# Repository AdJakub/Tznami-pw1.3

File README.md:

# Tznami-pw1.3
60% keyboard made for the half life project, week1 PCB.

## Why this?
I need a keyboard that will sit nicely on my desk setup, this one thanks to its custom usb slot placement will accomodate my cable management perfectly. 

## PCB
Schematic and PCB Made in kicad.
Schematic            |  PCB
:-------------------------:|:-------------------------:
  |  !

## Case
Made using fusion, using a sandwich mount and an oled mounting mechanism!

Uses stemma QT to connect the oled. connector to MCU and stripped cables soldered to the oled.

## Firmware

Comes with QMK and Vial support.

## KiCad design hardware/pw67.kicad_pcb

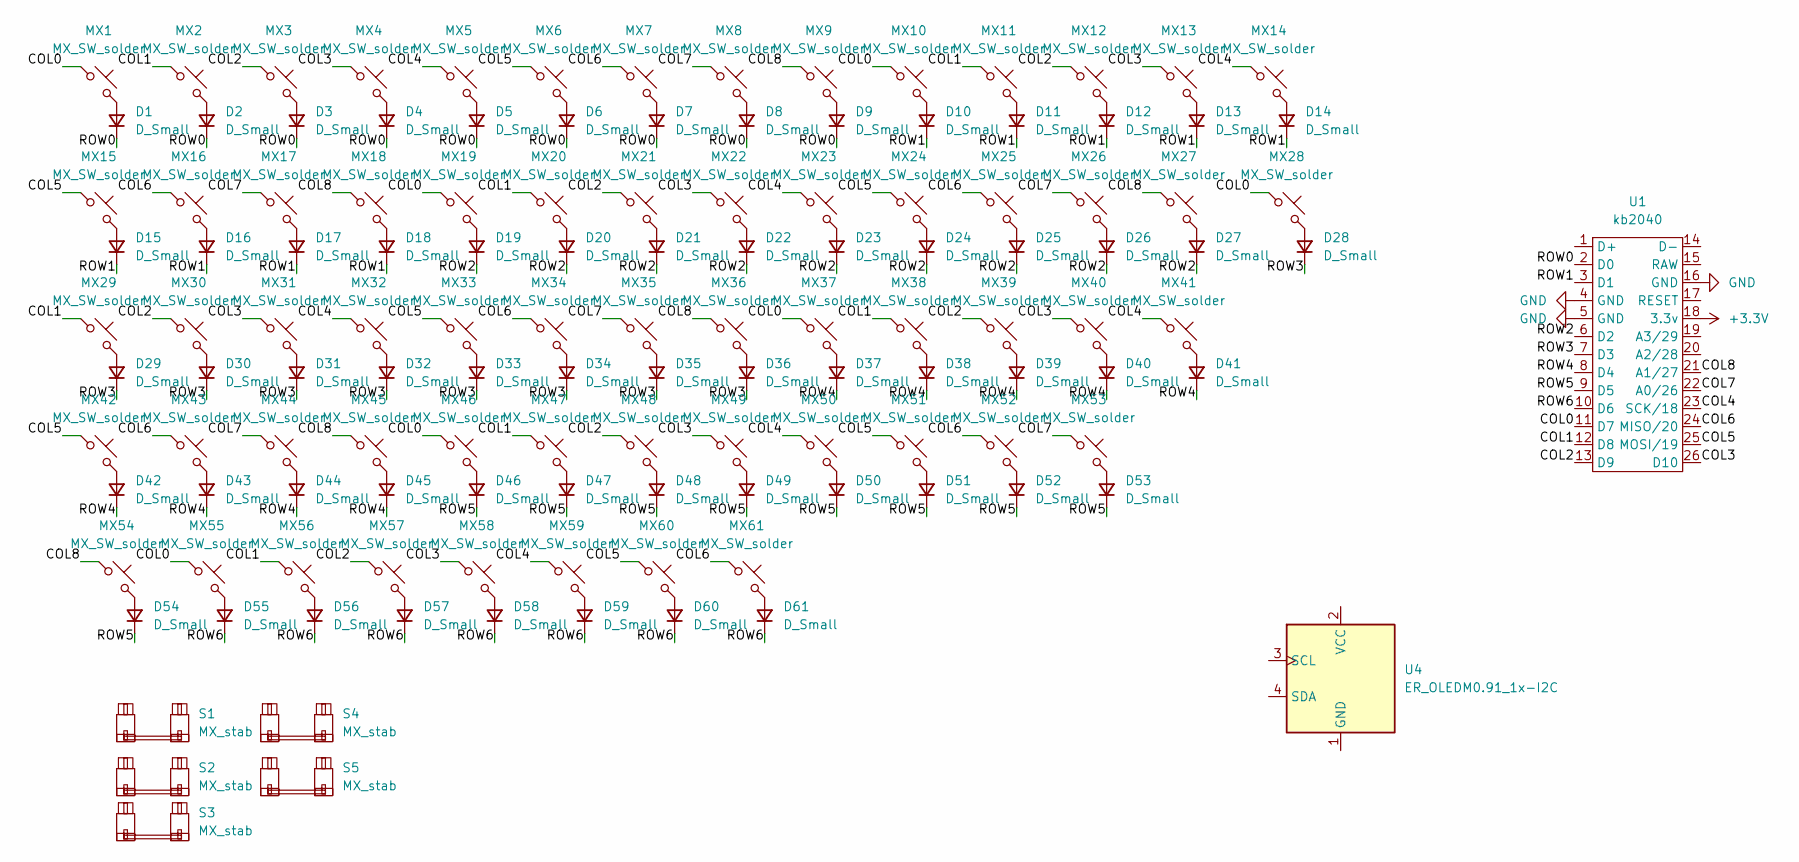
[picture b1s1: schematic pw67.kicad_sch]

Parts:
D1, D2, D3, D4, D5, D6, D7, D8, D9, D10, D11, D12, D13, D14, D15, D16, D17, D18, D19, D20, D21, D22, D23, D24, D25, D26, D27, D28, D29, D30, D31, D32, D33, D34, D35, D36, D37, D38, D39, D40, D41, D42, D43, D44, D45, D46, D47, D48, D49, D50, D51, D52, D53, D54, D55, D56, D57, D58, D59, D60, D61: D_Small; D_DO-35_SOD27_P7.62mm_Horizontal
MX1, MX2, MX3, MX4, MX5, MX6, MX7, MX8, MX9, MX10, MX11, MX12, MX13, MX14, MX16, MX17, MX18, MX19, MX20, MX21, MX22, MX23, MX24, MX25, MX26, MX27, MX29, MX30, MX31, MX32, MX33, MX34, MX35, MX36, MX37, MX38, MX39, MX40, MX41, MX42, MX43, MX44, MX45, MX46, MX47, MX48, MX49, MX50, MX51, MX52, MX53, MX57: MX_SW_solder; SW_MX_1u
MX15: MX_SW_solder; SW_MX_1.75u_STP_1.5
MX28: MX_SW_solder; SW_MX_1.5u
MX54, MX55, MX56, MX58, MX59, MX60, MX61: MX_SW_solder; SW_MX_1.25u
S1: MX_stab; STAB_MX_2u
S2, S3: MX_stab; STAB_MX_2.25u
S4: MX_stab; STAB_MX_2.75u
S5: MX_stab; STAB_MX_6.25u
U1: kb2040; KB2040_numbered
U4: ER_OLEDM0.91_1x-I2C

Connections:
+3.3V: U1.18 (3.3v)
/COL0: MX1.1, MX10.1, MX19.1, MX28.1, MX37.1, MX46.1, MX55.1, U1.11 (D7)
/COL1: MX2.1, MX11.1, MX20.1, MX29.1, MX38.1, MX47.1, MX56.1, U1.12 (D8)
/COL2: MX3.1, MX12.1, MX21.1, MX30.1, MX39.1, MX48.1, MX57.1, U1.13 (D9)
/COL3: MX4.1, MX13.1, MX22.1, MX31.1, MX40.1, MX49.1, MX58.1, U1.26 (D10)
/COL4: MX5.1, MX14.1, MX23.1, MX32.1, MX41.1, MX50.1, MX59.1, U1.23 (SCK/18)
/COL5: MX6.1, MX15.1, MX24.1, MX33.1, MX42.1, MX51.1, MX60.1, U1.25 (MOSI/19)
/COL6: MX7.1, MX16.1, MX25.1, MX34.1, MX43.1, MX52.1, MX61.1, U1.24 (MISO/20)
/COL7: MX8.1, MX17.1, MX26.1, MX35.1, MX44.1, MX53.1, U1.22 (A0/26)
/COL8: MX9.1, MX18.1, MX27.1, MX36.1, MX45.1, MX54.1, U1.21 (A1/27)
/ROW0: D1.1 (K), D2.1 (K), D3.1 (K), D4.1 (K), D5.1 (K), D6.1 (K), D7.1 (K), D8.1 (K), D9.1 (K), U1.2 (D0)
/ROW1: D10.1 (K), D11.1 (K), D12.1 (K), D13.1 (K), D14.1 (K), D15.1 (K), D16.1 (K), D17.1 (K), D18.1 (K), U1.3 (D1)
/ROW2: D19.1 (K), D20.1 (K), D21.1 (K), D22.1 (K), D23.1 (K), D24.1 (K), D25.1 (K), D26.1 (K), D27.1 (K), U1.6 (D2)
/ROW3: D28.1 (K), D29.1 (K), D30.1 (K), D31.1 (K), D32.1 (K), D33.1 (K), D34.1 (K), D35.1 (K), D36.1 (K), U1.7 (D3)
/ROW4: D37.1 (K), D38.1 (K), D39.1 (K), D40.1 (K), D41.1 (K), D42.1 (K), D43.1 (K), D44.1 (K), D45.1 (K), U1.8 (D4)
/ROW5: D46.1 (K), D47.1 (K), D48.1 (K), D49.1 (K), D50.1 (K), D51.1 (K), D52.1 (K), D53.1 (K), D54.1 (K), U1.9 (D5)
/ROW6: D55.1 (K), D56.1 (K), D57.1 (K), D58.1 (K), D59.1 (K), D60.1 (K), D61.1 (K), U1.10 (D6)
GND: U1.4 (GND), U1.5 (GND), U1.16 (GND)
unnamed: D1.2 (A), MX1.2
unnamed: D2.2 (A), MX2.2
unnamed: D3.2 (A), MX3.2
unnamed: D4.2 (A), MX4.2
unnamed: D5.2 (A), MX5.2
unnamed: D6.2 (A), MX6.2
unnamed: D7.2 (A), MX7.2
unnamed: D8.2 (A), MX8.2
unnamed: D9.2 (A), MX9.2
unnamed: D10.2 (A), MX10.2
unnamed: D11.2 (A), MX11.2
unnamed: D12.2 (A), MX12.2
unnamed: D13.2 (A), MX13.2
unnamed: D14.2 (A), MX14.2
unnamed: D15.2 (A), MX15.2
unnamed: D16.2 (A), MX16.2
unnamed: D17.2 (A), MX17.2
unnamed: D18.2 (A), MX18.2
unnamed: D19.2 (A), MX19.2
unnamed: D20.2 (A), MX20.2
unnamed: D21.2 (A), MX21.2
unnamed: D22.2 (A), MX22.2
unnamed: D23.2 (A), MX23.2
unnamed: D24.2 (A), MX24.2
unnamed: D25.2 (A), MX25.2
unnamed: D26.2 (A), MX26.2
unnamed: D27.2 (A), MX27.2
unnamed: D28.2 (A), MX28.2
unnamed: D29.2 (A), MX29.2
unnamed: D30.2 (A), MX30.2
unnamed: D31.2 (A), MX31.2
unnamed: D32.2 (A), MX32.2
unnamed: D33.2 (A), MX33.2
unnamed: D34.2 (A), MX34.2
unnamed: D35.2 (A), MX35.2
unnamed: D36.2 (A), MX36.2
unnamed: D37.2 (A), MX37.2
unnamed: D38.2 (A), MX38.2
unnamed: D39.2 (A), MX39.2
unnamed: D40.2 (A), MX40.2
unnamed: D41.2 (A), MX41.2
unnamed: D42.2 (A), MX42.2
unnamed: D43.2 (A), MX43.2
unnamed: D44.2 (A), MX44.2
unnamed: D45.2 (A), MX45.2
unnamed: D46.2 (A), MX46.2
unnamed: D47.2 (A), MX47.2
unnamed: D48.2 (A), MX48.2
unnamed: D49.2 (A), MX49.2
unnamed: D50.2 (A), MX50.2
unnamed: D51.2 (A), MX51.2
unnamed: D52.2 (A), MX52.2
unnamed: D53.2 (A), MX53.2
unnamed: D54.2 (A), MX54.2
unnamed: D55.2 (A), MX55.2
unnamed: D56.2 (A), MX56.2
unnamed: D57.2 (A), MX57.2
unnamed: D58.2 (A), MX58.2
unnamed: D59.2 (A), MX59.2
unnamed: D60.2 (A), MX60.2
unnamed: D61.2 (A), MX61.2

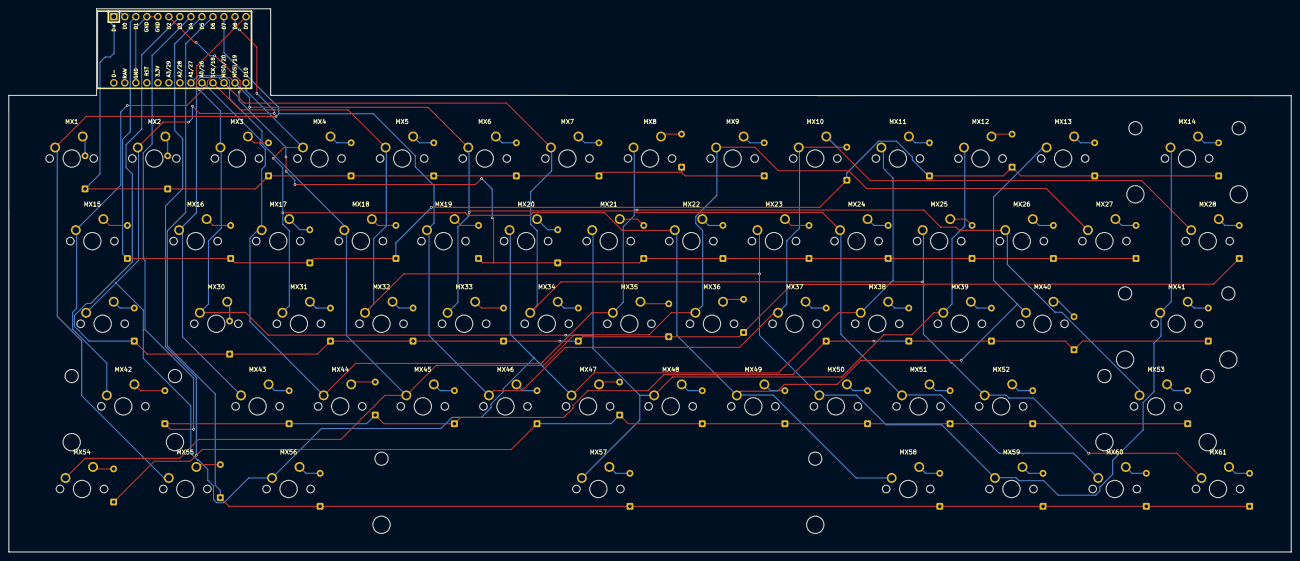
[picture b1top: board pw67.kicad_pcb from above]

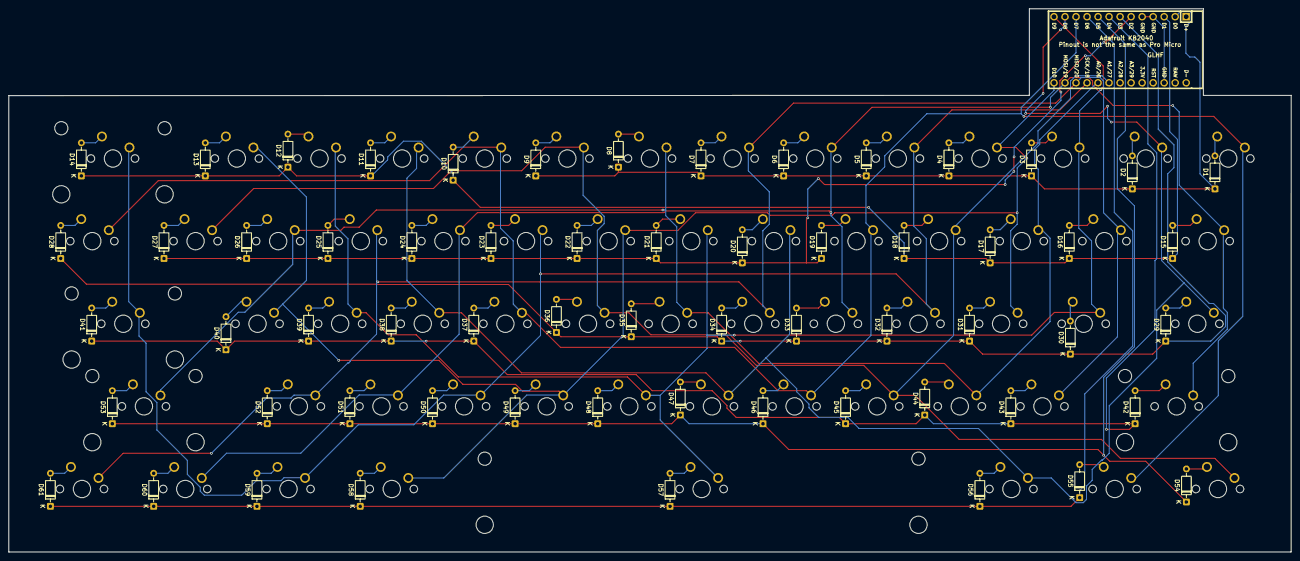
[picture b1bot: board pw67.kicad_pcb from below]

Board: 2 copper layers, 295.7 x 125.2 mm, 128 parts (62 on the bottom side), 78 nets.
